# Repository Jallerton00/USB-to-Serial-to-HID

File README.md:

# USB to Serial to HID

A tool which emulates a HID device (keyboard/mouse) to control one PC from another.

This can be used as the Keyboard and Mouse in a KVM - either an IP KVM (like PiKVM) or a laptop KVM.

## Images

## Usage

### PiKVM

The [PiKVM](https://github.com/pikvm/pikvm) project makes use of a Raspberry Pi to provide KVM over IP. Simply add an HDMI capture device and some way to do keyboard/mouse control. The PiKVM team provides a couple of ways of doing this, but this project is an alternative to it.

#### Set up

You need to be able to set the override.yaml in a PiKVM install. This typically means:

- Connect via SSH or the web terminal (`su -` to switch to root user)
- Enable read/write - `rw`
- Add the below config section - `nano /etc/kvmd/override.yaml`
    - [More information about the config files](https://docs.pikvm.org/first_steps/#structure-of-configuration-files)
- Make readonly - `ro`

```yaml
kvmd:
    hid:
        type: ch9329
```

#### Laptop KVM

There exists a project which uses a piece of custom hardware to turn a laptop into a KVM - [Openterface](https://openterface.com/) - which means you can use your laptop as a PC crash cart. This project can be used as a cheaper alternative.

With a USB HDMI capture device (like [this](https://www.amazon.co.uk/UGREEN-Thunderbolt-Compatible-Camera-iPad-Laptop-Phone/dp/B0CFQ2BMPZ)), this hardware and a [fork of the Openterface software](https://github.com/Jallerton00/Openterface_QT), you can mimic most of what the Openterface project can achieve.

This is not feature complete - the original project provides more options for host software; a USB port swhich which can be switched between host and target & integrated HDMI capture - but may be a decent alternative for some.

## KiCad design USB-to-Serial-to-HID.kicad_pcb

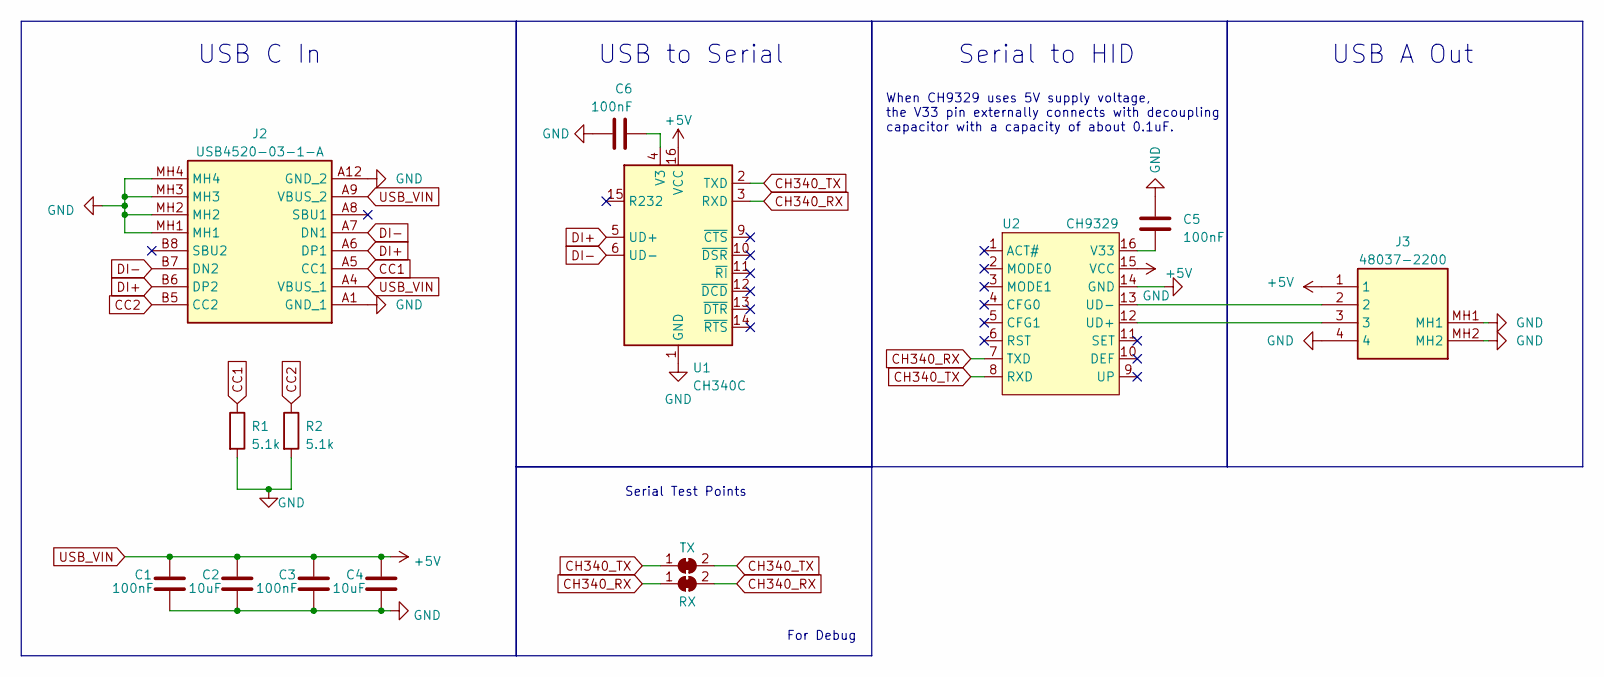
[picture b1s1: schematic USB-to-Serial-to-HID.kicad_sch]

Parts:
C1, C3, C5, C6: 100nF; C_0805_2012Metric_Pad1.18x1.45mm_HandSolder
C2, C4: 10uF; C_0805_2012Metric_Pad1.18x1.45mm_HandSolder
J2: USB4520-03-1-A; USB4520031A; Manufacturer_Part_Number USB4520-03-1-A
J3: 48037-2200; 480372200; Manufacturer_Part_Number 48037-2200
JP1: TX; TestPoint_2Pads_Pitch2.54mm_Drill0.8mm
JP2: RX; TestPoint_2Pads_Pitch2.54mm_Drill0.8mm
R1, R2: 5.1k; R_0805_2012Metric_Pad1.20x1.40mm_HandSolder
U1: CH340C; SOIC-16_3.9x9.9mm_P1.27mm
U2: CH9329; SOIC-16_3.9x9.9mm_P1.27mm

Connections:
CC1: J2.A5 (CC1), R1.1
CC2: J2.B5 (CC2), R2.1
CH340_RX: JP2.1 (A), JP2.2 (B), U1.3 (RXD), U2.7 (TXD)
CH340_TX: JP1.1 (A), JP1.2 (B), U1.2 (TXD), U2.8 (RXD)
DI+: J2.A6 (DP1), J2.B6 (DP2), U1.5 (UD+)
DI-: J2.A7 (DN1), J2.B7 (DN2), U1.6 (UD-)
GND: C1.2, C2.2, C3.2, C4.2, C5.1, C6.1, J2.A1 (GND_1), J2.A12 (GND_2), J2.MH1, J2.MH2, J2.MH3, J2.MH4, J3.4, J3.MH1, J3.MH2, R1.2, R2.2, U1.1 (GND), U2.14 (GND)
unnamed: C6.2, U1.4 (V3)
unnamed: J3.3, U2.12 (UD+)
unnamed: J3.2, U2.13 (UD-)
unnamed: C5.2, U2.16 (V33)
USB_VIN: C1.1, C2.1, C3.1, C4.1, J2.A4 (VBUS_1), J2.A9 (VBUS_2), J3.1, U1.16 (VCC), U2.15 (VCC)

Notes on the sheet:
Serial Test Points
USB C In
When CH9329 uses 5V supply voltage, the V33 pin externally connects with decoupling capacitor with a capacity of about 0.1uF.
Serial to HID
USB A Out
USB to Serial
For Debug

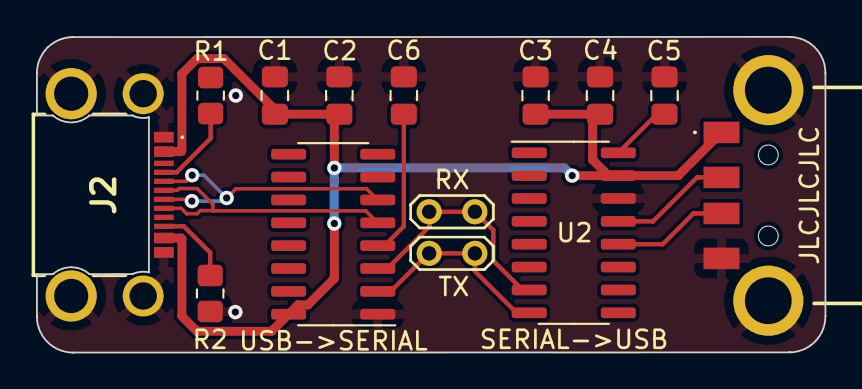
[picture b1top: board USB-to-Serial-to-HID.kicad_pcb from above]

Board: 2 copper layers, 43.8 x 17.5 mm, 14 parts (0 on the bottom side), 12 nets.

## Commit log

2024-07-07 Initial Commit (After adding caps)
2024-07-07 Update images, schematic and gerbers
2024-07-07 Rename to USB-to-Serial-to-HID
2024-07-07 More renaming
2024-07-07 Rename output zip
2024-07-08 Move to CH340C
2024-07-09 Make shape path relative
2024-07-09 Make USB step file path relative
2024-07-09 Update 480372200.kicad_mod and PCB
2024-07-09 Update PCB - USB Step File
2025-05-10 Update to use target 5V as well as host 5V
